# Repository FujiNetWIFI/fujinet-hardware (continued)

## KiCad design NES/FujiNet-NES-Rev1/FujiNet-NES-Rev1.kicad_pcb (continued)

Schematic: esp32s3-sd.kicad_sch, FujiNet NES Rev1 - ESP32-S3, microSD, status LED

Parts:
C42: 22uF; C_0805_2012Metric; MPN CL21A226MAQNNNE; LCSC C45783
C43, C46: 100nF; C_0603_1608Metric; MPN CC0603KRX7R9BB104; LCSC C14663
C44: 1uF; C_0603_1608Metric; MPN CL10A105KB8NNNC; LCSC C15849
C45: 10uF; C_0603_1608Metric; MPN CL10A106KP8NNNC; LCSC C19702
D3: WS2812B-2020-V6; LED_WS2812B-2020_PLCC4_2.0x2.0mm; MPN WS2812B-2020-V6; LCSC C52917434
J2: microSD; TF-SMD_TF-015; MPN TF-015; LCSC C113206
R17, R18: 10k; R_0603_1608Metric; MPN 0603WAF1002T5E; LCSC C25804
R19: 330R; R_0603_1608Metric; MPN 0603WAF3300T5E; LCSC C23138
RN1: 4x10k; R_Array_Convex_4x0603; MPN 4D03WGJ0103T5E; LCSC C29718
SW3: S3_RST; SW_SPST_TL3342; MPN TL3342F160QG; LCSC C2886898
SW4: S3_BOOT; SW_SPST_TL3342; MPN TL3342F160QG; LCSC C2886898
U4: ESP32-S3-WROOM-1-N16R8; ESP32-S3-WROOM-1; MPN ESP32-S3-WROOM-1-N16R8; LCSC C2913202

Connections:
+3V3: C42.1, C43.1, C45.1, J2.4 (VDD), R17.1, R18.1, RN1.5 (R4.2), RN1.6 (R3.2), RN1.7 (R2.2), RN1.8 (R1.2), U4.2 (3V3); also elsewhere on the board
+5V: C46.1, D3.4 (VDD); also elsewhere on the board
BOOTSEL_CTL: U4.5 (IO5); also elsewhere on the board
GND: C42.2, C43.2, C44.2, C45.2, C46.2, D3.2 (VSS), J2.6 (VSS), J2.10 (SH), J2.11 (SH), J2.12 (SH), J2.13 (SH), SW3.2, SW4.2, U4.1 (GND), U4.40 (GND), U4.41 (GND); also elsewhere on the board
LED_STRIP: R19.1, U4.25 (IO48)
RUN_CTL: U4.4 (IO4); also elsewhere on the board
S3_EN: C44.1, R17.2, SW3.1, U4.3 (EN); also elsewhere on the board
S3_IO0: SW4.1, U4.27 (IO0); also elsewhere on the board
S3_RXD: U4.36 (RXD0); also elsewhere on the board
S3_TXD: U4.37 (TXD0); also elsewhere on the board
SD_CD: J2.9 (CD), R18.2, U4.35 (IO42)
SD_CS: J2.2 (DAT3/CS), RN1.1 (R1.1), U4.34 (IO41)
SD_DAT1: J2.8 (DAT1), RN1.3 (R3.1)
SD_DAT2: J2.1 (DAT2), RN1.4 (R4.1)
SD_MISO: J2.7 (DAT0/DO), RN1.2 (R2.1), U4.33 (IO40)
SD_MOSI: J2.3 (CMD/DI), U4.31 (IO38)
SD_SCK: J2.5 (CLK), U4.32 (IO39)
USB_DM: U4.13 (USB_D-); also elsewhere on the board
USB_DP: U4.14 (USB_D+); also elsewhere on the board
WS_DIN: D3.3 (DIN), R19.2

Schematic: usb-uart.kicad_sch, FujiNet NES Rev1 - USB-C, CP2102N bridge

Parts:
C47: 1uF; C_0603_1608Metric; MPN CL10A105KB8NNNC; LCSC C15849
C48, C49: 100nF; C_0603_1608Metric; MPN CC0603KRX7R9BB104; LCSC C14663
C50: 4.7uF; C_0603_1608Metric; MPN CL10A475KO8NNNC; LCSC C19666
D4, D5, D6: ESD5Z5.0T1G; D_SOD-523; MPN ESD5Z5.0T1G; LCSC C82044
J3: USB-C; USB_C_Receptacle_HRO_TYPE-C-31-M-12; MPN TYPE-C-31-M-12; LCSC C165948
R20, R21: 5.1k; R_0603_1608Metric; MPN 0603WAF5101T5E; LCSC C23186
R22: 22k; R_0603_1608Metric; MPN 0603WAF2202T5E; LCSC C31850
R23: 47k; R_0603_1608Metric; MPN 0603WAF4702T5E; LCSC C25819
R24: 10k; R_0603_1608Metric; MPN 0603WAF1002T5E; LCSC C25804
U5: CP2102N-A02-GQFN28; QFN-28-1EP_5x5mm_P0.5mm_EP3.35x3.35mm; MPN CP2102N-A02-GQFN28R; LCSC C964632
U6: UMH3N; SOT-363_SC-70-6; MPN UMH3N; LCSC C62892

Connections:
+3V3: C49.1, C50.1, R24.1, U5.6 (VDD), U5.7 (VREGIN); also elsewhere on the board
CC1: J3.A5 (CC1), R20.1
CC2: J3.B5 (CC2), R21.1
CP_RST: R24.2, U5.9 (~RST)
GND: C47.2, C48.2, C49.2, C50.2, D4.2 (A), D5.2 (A), D6.2 (A), J3.A1 (GND), J3.A12 (GND), J3.B1 (GND), J3.B12 (GND), J3.SH (SHIELD), R20.2, R21.2, R23.2, U5.3 (GND), U5.23 (~CTS), U5.29 (GND); also elsewhere on the board
S3_EN: U6.6 (C1); also elsewhere on the board
S3_IO0: U6.3 (C2); also elsewhere on the board
S3_RXD: U5.26 (TXD); also elsewhere on the board
S3_TXD: U5.25 (RXD); also elsewhere on the board
UART_DTR: U5.28 (~DTR), U6.2 (B1), U6.4 (E2)
UART_RTS: U5.24 (~RTS), U6.1 (E1), U6.5 (B2)
UBRG_DM: D5.1 (K), J3.A7 (D-), J3.B7 (D-), U5.5 (D-)
UBRG_DP: D4.1 (K), J3.A6 (D+), J3.B6 (D+), U5.4 (D+)
VBUS: C47.1, C48.1, D6.1 (K), J3.A4 (VBUS), J3.A9 (VBUS), J3.B4 (VBUS), J3.B9 (VBUS), R22.1; also elsewhere on the board
VBUS_SNS: R22.2, R23.1, U5.8 (VBUS)

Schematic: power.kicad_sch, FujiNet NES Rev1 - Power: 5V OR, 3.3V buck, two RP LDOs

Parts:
C51, C55, C56: 100nF; C_0603_1608Metric; MPN CC0603KRX7R9BB104; LCSC C14663
C52, C53, C54, C57, C58: 22uF; C_0805_2012Metric; MPN CL21A226MAQNNNE; LCSC C45783
C59, C60, C61, C62: 1uF; C_0603_1608Metric; MPN CL10A105KB8NNNC; LCSC C15849
D7: SS34; D_SMA; MPN SS34; LCSC C8678
L3: 6.8uH; L_Sunlord_SWPA4030S; MPN SWPA4030S6R8MT; LCSC C62684
Q1: AO3401A; SOT-23; MPN AO3401A; LCSC C15127
R25: 4.7k; R_0603_1608Metric; MPN 0603WAF4701T5E; LCSC C23162
U7: AP63203WU; TSOT-23-6; MPN AP63203WU-7; LCSC C780769
U8, U9: AP2112K-3.3; SOT-23-5; MPN AP2112K-3.3TRG1; LCSC C51118

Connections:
+3V3: C57.1, C58.1, L3.2, U7.1 (FB); also elsewhere on the board
+3V3_RP: C60.1, U8.5 (VOUT); also elsewhere on the board
+3V3_RPB: C62.1, U9.5 (VOUT); also elsewhere on the board
+5V: C52.1, C53.1, C54.1, C55.1, C59.1, C61.1, D7.1 (K), Q1.2 (S), U7.2 (EN), U7.3 (IN), U8.1 (VIN), U8.3 (EN), U9.1 (VIN), U9.3 (EN); also elsewhere on the board
BUCK_BST: C56.2, U7.6 (BST)
BUCK_SW: C56.1, L3.1, U7.5 (SW)
CONS_5V: C51.1, Q1.3 (D); also elsewhere on the board
GND: C51.2, C52.2, C53.2, C54.2, C55.2, C57.2, C58.2, C59.2, C60.2, C61.2, C62.2, R25.2, U7.4 (GND), U8.2 (GND), U9.2 (GND); also elsewhere on the board
VBUS: D7.2 (A), Q1.1 (G), R25.1; also elsewhere on the board

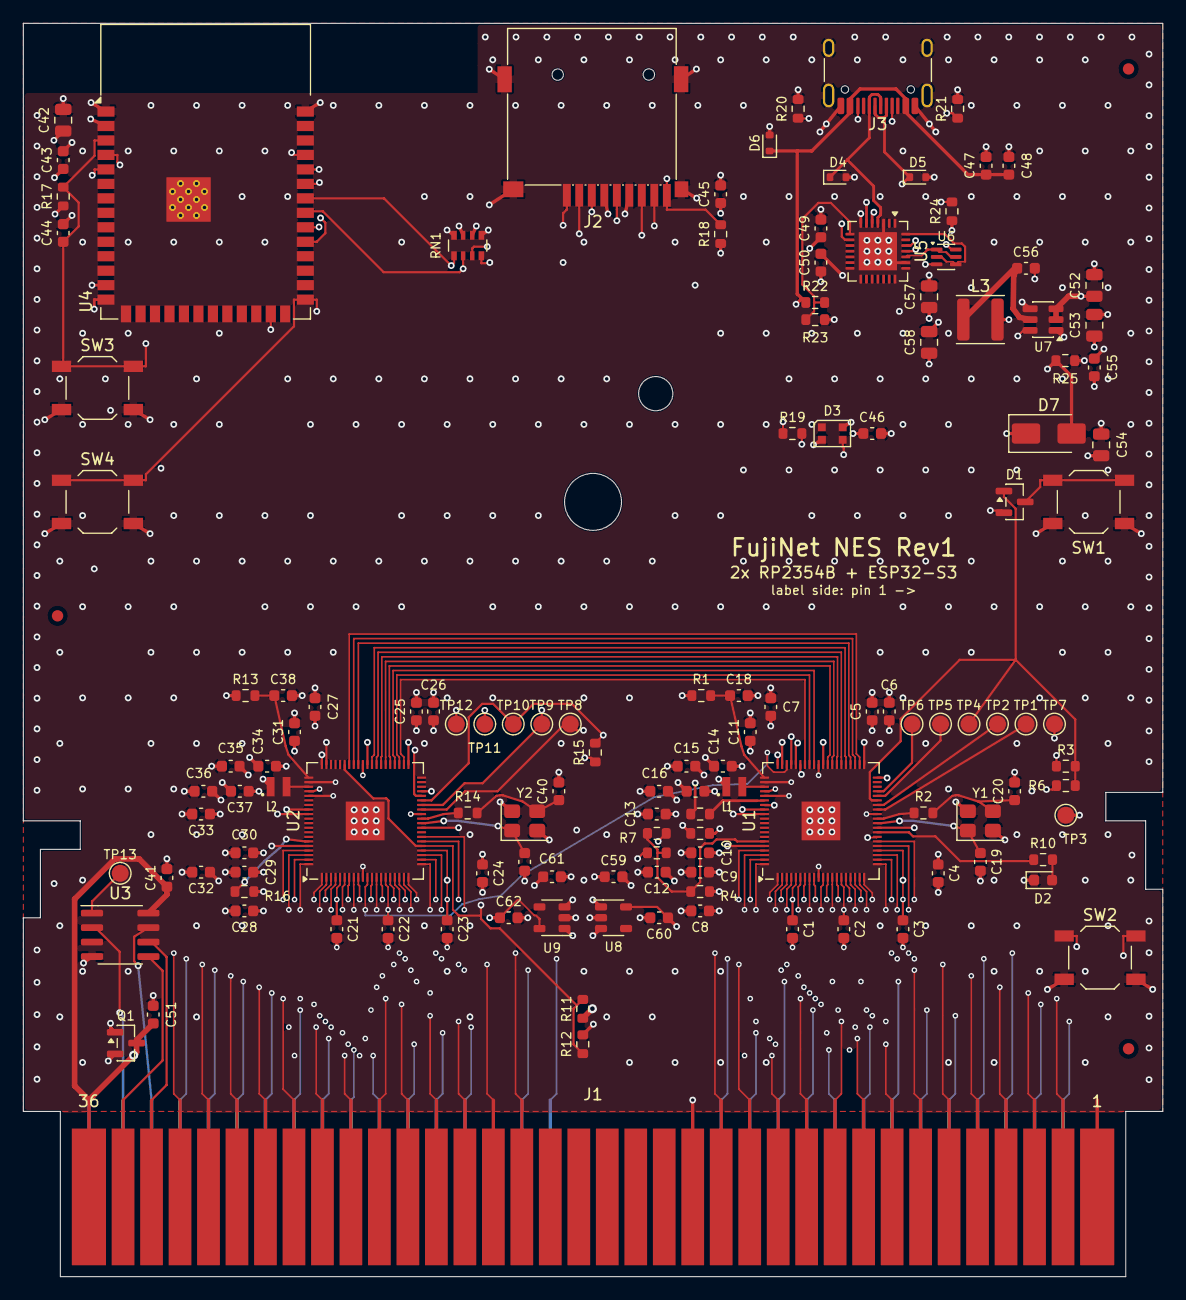
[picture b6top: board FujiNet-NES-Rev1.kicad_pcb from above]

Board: 6 copper layers, 100.0 x 110.0 mm, 133 parts (0 on the bottom side), 134 nets.

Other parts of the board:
FID1, FID2, FID3: Fiducial_1mm_Mask2mm

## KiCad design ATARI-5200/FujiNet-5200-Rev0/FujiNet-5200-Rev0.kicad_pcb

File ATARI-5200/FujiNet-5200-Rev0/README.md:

# FujiNet-5200 Rev0

An all-in-one **Atari 5200 FujiNet cartridge**: one board in the 36-pin cartridge slot that
carries both halves of the FujiNet stack.

**The cart half: RP2354B** (RP2350B + 2 MB flash, QFN-80) at 200 MHz.

- Runs the `fuji5200` cart firmware from `fujinet-firmware/pico/atari-5200`.
- Reads A0-A13 and the two cart enables (/EN40, /EN80) straight off the console's 5 V bus,
  through its 5 V-tolerant pads (GPIO0-15), and follows them as a mask ROM would.
- Puts each byte on GPIO16-23, into a **74HCT541** whose outputs are the edge's D0-D7.
- A **74HCT08 + 74HCT14** opens the '541 only while all three hold: an enable is low, the console
  is powered (PWR_OK), and the RP says it is serving (BUF_EN).
- A **74LVC1G17** squares the 2-port console's diode-isolated PHI2.

**The FujiNet half: ESP32-S3-WROOM-1-N16R8**, running the `fujiversal-atari5200` build of
fujinet-firmware.

- It is the RP's USB host on IO19/IO20, and it re-flashes the RP over PICOBOOT.
- USB-C: power, plus a CP2102N UART with UMH3N auto-program.
- microSD, a WS2812B status LED, and RESET / BOOTSEL / S3 EN / S3 BOOT buttons.

**Power:** +5V is the OR of three sources:

- the console's 5 V, through a P-FET;
- USB VBUS;
- the universal consoles' raw adapter DC on edge pin 11, through a 5 V buck.

The console path switches off whenever either of the other two is present.

**Status (2026-10-09):** schematic regenerated and audited; board placed, routed and packaged for
JLCPCB and PCBWay. Not yet built. See *Before ordering* and *Bring-up*.

| Check | Result |
|---|---|
| ERC, all severities | 0 |
| `tools/check_nets.py`: netlist vs `a52_cart.h`, the CX5200 FSM edge map, the S3 pin map, FT-pad rules | 366 / 366 |
| `tools/check_glue.py`: the '541 enables vs `a52_glue_drive()`, every input | 16 / 16 |
| Netlist parity: drawn sheets vs `design.py`, names included | every net |
| Mirror check: each sheet's parts in board order | tau 1.00 on all five sheets |
| `tools/audit/edge_orientation.py` | OK |
| Deep review (kicad-happy evidence gate) | 30 / 30 findings verified against datasheet pages |
| kicad-happy SPICE + `tools/audit/spice_checks.py` | 21 / 21; PHI2, PWR_OK and console-gate decks pass |
| DRC with schematic parity, all severities | 0 violations, 0 unconnected, 0 parity issues |
| `tools/audit/check_fab.py` / `check_gerbers.py` | 14 / 14 / all pass |
| JLCPCB stock (`tools/audit/sourcing.py`) | 46 lines, 0 short for 5 boards; ~US$17 of parts per board |

## Sheets

The schematic is drawn the way the board is built. Every sheet is the board turned so that the
fingers face left (board south -> page left, north -> right, west -> top, east -> bottom), with
each part where it sits on the board. Signals flow left to right, from the cartridge slot to the
USB-C. `tools/sch_place.py` holds every sheet to the board's order.

| Page | Sheet | Contents |
|---|---|---|
| 1 | root | the board outline with a block per sheet, the nine signals between sheets, notes |
| 2 | `cart-bus` | the 36-pin edge, 74HCT541, the '08 / '14 glue, the RP2354B's GPIOs, PHI2 buffer, interlock, PWR_OK and ADC senses, debug UART, scope pads |
| 3 | `rp-core` | RP2354B supplies and decoupling ring, core regulator, crystal, SWD, RUN / BOOTSEL, USB to the S3 |
| 4 | `fujinet` | ESP32-S3, microSD, WS2812B, S3 EN / BOOT |
| 5 | `usb` | USB-C, CP2102N, auto-program pair |
| 6 | `power` | the three-source +5V OR, the raw-DC buck, the 3.3 V buck, the RP's LDO |

## Edge connector

The edge pinout is taken from Atari's CX5200 Field Service Manual (Rev 4, 1983). It has
schematics of CA018087 (the original 4-port), CA020108 (the universal 4-port) and CA021374 (the
2-port).

The geometry is from Grand Idea Studio's Pixels Past gerbers, tdididit's a52 library, sanni's
cartreader adapter, and the Sullins connector datasheet. `tools/audit/edge_orientation.py`
checks the footprint against them.

| Pin | Signal | Net | Pin | Signal | Net |
|---|---|---|---|---|---|
| 1-8 | D0-D7 | '541 Y | 19, 20 | A0, A1 | GPIO0, 1 |
| 9 | /Enable $80-$BF | EN80_N | 21, 22 | A3, A4 | GPIO3, 4 |
| 10 | /Enable $40-$7F | EN40_N | 23 | GND (shield) | GND |
| 11 | raw DC (universal boards) | UNREG -> JP2 -> PTC -> buck | 24 | GND (CA018087) / video in (universal) | **open** |
| 12, 13 | GND | GND | 25 | GND | GND |
| 14 | GND (CA018087) / PHI2 (2-port, via CR9) | PHI2 -> 74LVC1G17 | 26 | +5 V from VR1 | CONS_5V |
| 15, 16, 17 | A6, A5, A2 | GPIO6, 5, 2 | 27, 29, 31 | A7, A8, A9 | GPIO7, 8, 9 |
| 18 | CI1, interlock (short finger) | ILK_A, JP1 | 28, 30 | NC, OSC (universal) | **open** |
| | | | 32-35 | A13, A10, A12, A11 | GPIO13, 10, 12, 11 |
| | | | 36 | CI2, interlock (short finger) | ILK_B, JP1 |

**Faces.** Pins 1-18 are on the label face, which is F.Cu, the component side. Pin 1 (D0) is at
the left when seen from that face with the fingers down. Pin 37-k sits behind pin k.

**Short fingers.** Pins 18 and 36 start 1.9 mm from the edge; the others start at 0.6 mm. They
make contact last and break first, as on every stock cart.

**No R/W, and the enables are not PHI2-qualified.** The enables are plain 74LS139 decodes of A14
/ A15. The cart answers reads only, and the '541 drives whenever an enable is low, exactly as a
stock ROM does.

**Never ground 11, 24, 28 or 30.**

- 11 is the adapter's raw DC on the universal boards, live even with the console switched off.
- 24 is the VCS adaptor's video input on the universal boards.
- 30 goes into the colour oscillator.

## RP2354B pin map

The pin map is exactly `a52_cart.h`. `tools/check_nets.py` reads every `*_PIN` define and fails
if the header names a pin this board does not wire, or the board wires one the header does not
name.

| GPIO | Net | Goes to |
|---|---|---|
| 0-13 | A0-A13 | the edge, directly |
| 14, 15 | EN40_N, EN80_N | edge 10, 9; also the 74HCT08 |
| 16-23 | RP_D0-7 | 74HCT541 A8..A1 (channels reversed; outputs only) |
| 24 | PWR_OK | 74HCT14 output (console 5 V sense) |
| 25 | PHI2_RP | 74LVC1G17 output (2-port only) |
| 26 | BUF_EN | the glue; R25 4.7k pull-down (RP2350-E9) |
| 27 | RP_LED | 1k, red LED |
| 28 | ILK | the DNP interlock switch's driver |
| 40 | VSENSE_ADC | ADC0: CONS_5V through 100k / 100k (0.5 x), 100 nF |
| 44, 45 | DBG_TX, DBG_RX | J4 (DNP), 3.3 V only |

- GPIO40-47 are not 5 V tolerant. `check_nets.py` asserts that only passives and the 3.3 V debug
  header reach them.
- The bus inputs have no pulls. The firmware turns the pad pulls off (RP2350 erratum E9).

## Glue

`a52_glue_drive()`: `drive = !(en40_n && en80_n) && pwrok && bufen`.

```
/OE1 = EN_ANY_N = /EN40 AND /EN80        74HCT08: either enable low
/OE2 = SERVE_N  = NOT(PWR_OK AND BUF_EN) 74HCT08 + 74HCT14: console powered and the RP serving
```

- **PWR_OK.** CONS_5V goes through 22k / 100k into a 74HCT14 Schmitt and is inverted twice. It
  is high once the console rail passes 2.3-2.6 V.
- **BUF_EN.** A 4.7k pull-down keeps the '541 shut until the firmware drives GPIO26. That is
  under the 8.2k the RP2350-E9 latch needs.
- **PHI2 (2-port).** The console reaches pin 14 through CR9, a 1N914 with its anode at the pin,
  so it can only pull PHI2 low, to 0.94-1.09 V. R29 4.7k pulls the pin up to CONS_5V, and U11, a
  74LVC1G17 at 5 V, squares it: VT- min 1.32 V, +0.24 V of margin at the worst corner.

  The pull-up goes to CONS_5V and not +5V. With the console off and USB on, a pull-up to +5V
  would feed the console's LS125 through CR9.

## Power

**Q3, AO3401A: console 5 V -> +5V.** D = CONS_5V, S = +5V, gate = CONS_OFF.

- CONS_OFF = VBUS OR PRE5V, through D9 (BAT54C), with R23 100k to GND.
- The console path is fully on whenever the console alone powers the cart.
- R3 and R22, 4.7k each, keep the SS34s' reverse leakage off the OR. At 500 uA each, VGS is still
  -2.9 V.

**D4, SS34: USB VBUS -> +5V.**

**Edge 11 raw DC -> +5V.** The chain is:

1. JP2, a bridged jumper. Cut it to take nothing from pin 11.
2. F1, a 0.35 A / 30 V PTC.
3. R30, 2.2R, to limit inrush when the cart goes in with the adapter live.
4. U10, an AP63205 (5 V, 3.8-32 V in).
5. D8, an SS34.

On the universal consoles this takes the whole cart off VR1.

**+5V feeds:**

- the '541, '08, '14 and LVC1G17;
- the WS2812B;
- the AP2112K LDO (+3V3_RP, every RP2354B supply pin), which rises with +5V;
- the AP63203 buck (+3V3: S3, microSD, CP2102N).

**Budget:** ~470 mA at a WiFi TX burst, ~170 mA on average (`tools/audit/margins.py`).

**Warning: the original 4-port console (CA018087).** VR1 there is a **0.5 A 78M05** that also
feeds the console's RAM and controllers, and that board has no raw DC on pin 11. Without USB, a
WiFi burst can pull VR1 into current limit. On those consoles, run with USB-C plugged in for
WiFi. The universal consoles (CA020108, CA021374) feed the cart from the adapter instead.

## Interlock

Pins 18 and 36 are shorted by **JP1**, a bridged solder jumper, as a stock cartridge shorts them.
The stock jumper closes Q8 / Q6's base circuit (34-61 mA at ~0.2 V), which switches VR1 on.

Beside JP1, all DNP:

- **Q2**, a 2N7002 low-side switch: D on 36, S on 18, gate pulled to +5V by R26.
- **Q1**, a 2N7002 driver on GPIO28.
- **R24**, a 4.7k pull-down on GPIO28.

To let the firmware open the interlock (a console power cycle), cut JP1 and fit them. The cart
must then be powered from USB or the raw DC first, since VR1 is what that switch turns on.

## Board

**Outline.** T-shaped, 84 x 98 mm (`tools/placement.py`, `docs/floorplan-study.md`):

- the 47.8 mm tab;
- the original cart board's 61 mm lower body, up to 38 mm from the edge;
- a 45-degree step out to the 84 mm upper body that carries the FujiNet half.

It needs a custom shell. The stock 5200 shell holds a 61 x 89.5 mm board between ribs.
`case/board-anchors.scad` gives a shell design the outline, the three screws, the button
pinholes, the LEDs, the USB-C / microSD / antenna openings and a label recess.

**Stack-up.** 6 layers, 1.6 mm:

| Layer | Use |
|---|---|
| F.Cu | every part; fingers 1-18; signals and a GND pour |
| In1 | GND |
| In2, In3 | signals |
| In4 | power: +3V3 north; a +5V island south and east; +3V3_RP under the RP2354B ring; DVDD under its core |
| B.Cu | fingers 19-36; signals and a GND pour |

**Data path.** The 74HCT541 stands over the D0-D7 fingers, and its channels are taken in
reverse, so finger -> '541 -> RP GPIO16-23 crosses nothing on F.Cu.

## Fab packages

`tools/export.py` writes them, and `tools/audit/check_fab.py` / `check_gerbers.py` check them.

- `exports/jlcpcb/`: `ORDER-JLCPCB.md`, gerbers with an order-number spot, `BOM-JLCPCB.csv`, and
  `CPL-JLCPCB.csv` with rotations corrected to each LCSC part's EasyEDA footprint
  (`tools/audit/jlc/`, measured pad by pad).
- `exports/pcbway/`: `ORDER-PCBWay.md`, gerbers, `BOM-PCBWay.csv` (MPN / manufacturer),
  `Centroid-PCBWay.csv` (KiCad's own rotations), and `Assembly-top.pdf`.

Both need:

- 6 layers, 1.6 mm, ENIG;
- **hard gold fingers with a 30-45 degree bevel** on the 47.8 mm tab edge only;
- via-in-pad filled and capped under the RP2354B;
- top-side assembly.

## Before ordering

1. **The tab.** Print `docs/tab-overlay-1to1.pdf` at 100 % and check its 50 mm ruler. Lay a real
   5200 cartridge board on it:
   - pins 1-18 on the label side, pin 1 at the left;
   - the finger span, the 47.8 mm tab and the two short fingers must match.
2. **Thickness.** The console connector takes 1.57 +/- 0.2 mm. 1.6 mm is ordered.
3. **Stock.** Re-run `tools/audit/sourcing.py` on the order day.
4. **The preview.** In JLCPCB's placement preview, check:
   - pin 1 of the RP2354B, the '541 (TSSOP-20), the '08 / '14, the LVC1G17 (SOT-353), the
     regulators, the CP2102N, USB-C and the microSD;
   - the polarity of the diodes and the WS2812B.

## Bring-up

1. **Power, no console.**
   - USB-C only: +5V is 4.3-4.9 V at TP2, +3V3 at TP1, +3V3_RP at TP11, DVDD 1.1 V at TP3.
   - CONS_5V (TP17) and PRE5V (TP16) stay at 0 V.
2. **In a 2-port or universal 4-port, USB unplugged.**
   - With the adapter in, TP18 (raw DC after the PTC) reads 9-13 V and PRE5V 5.0 V.
   - The console path is off: CONS_5V carries only the console's own 5 V.
   - Cut JP2 and the cart runs from CONS_5V instead.
3. **In an original 4-port (CA018087), USB unplugged.** Measure CONS_5V at TP17 during WiFi TX.
   If VR1 sags, run WiFi on USB power, or cap the S3's TX power in firmware.
4. **Bus.** Scope /EN40, /EN80 (TP8 / TP9), /OE1 / /OE2 (TP10 / TP13), PWR_OK (TP14) and D0.
   Check:
   - the '541 opens only inside an enable;
   - D0 settles well before the end of the cycle (`timing_margins.py`: +234 ns budget).
5. **PHI2 (2-port).** At TP15 the pin sits at ~1 V low and ~4.8 V high. PHI2_RP (GPIO25) is a
   clean 0 / 5 V square.
6. **Power-on race.** Measure the RP's cold boot to a serving core1 against the 5200 BIOS's first
   cart read (scope BUF_EN against /EN80 at power-on). USB-C power before the console avoids the
   race.

## Flashing

- **The S3:** over USB-C (CP2102N, esptool auto-program).
- **The RP:**
  - by the S3 over PICOBOOT: IO4 -> 1k -> RUN, IO5 -> 1k -> QSPI_SS, low to assert;
  - by hand: hold BOOTSEL (SW2) and press RESET (SW1);
  - over SWD: TP4 SWCLK, TP5 SWDIO, TP6 GND, TP7 RUN.
- **The RP's debug UART:** J4 (DNP, 3-pin 2.54 mm, 3.3 V).

## Firmware follow-ups (not changed here)

- **fn-5200-board `fujiversal-atari5200.h`:**
  - add `PIN_RP2040_RUN` = IO4 and `PIN_RP2040_BOOTSEL` = IO5, which this board wires;
  - set `PIN_CARD_DETECT` to IO42 (the microSD card-detect, 10k pull-up).
- **`a52_cart.h`:** `VSENSE_PIN`'s comment says "12 V-safe divider". Pin 26 is 5 V and the
  divider is 0.5 x. Nothing reads the ADC yet. It could watch VR1 sag during WiFi.
- **`main.c`:** nothing initialises GPIO44/45 (J4).
- **S3:** cap the TX power when the cart runs from VR1 alone (an original 4-port without USB).

## Regenerating

You need KiCad 10.0.6, Python 3 with numpy, a C compiler (for `check_glue.py`), ngspice and
poppler for the audits, and Java with Freerouting 2.4.1 for the board.

```sh
tools/build_all.sh                 # footprints, sheets, ERC, check_nets / check_glue / edge, BOM, PDF, fab packages
LAYOUT=1 tools/build_all.sh        # ... and place, route (tools/route_board.sh) and DRC the board
tools/audit/run_sch_audit.sh       # kicad-happy schematic audit, SPICE, margins, timing, deep review
tools/audit/run_pcb_audit.sh       # kicad-happy PCB, cross, EMC, thermal, gerbers, release gate
```

`check_*.py` read two external sources:

- `$FUJINET_FIRMWARE/pico/atari-5200` (default `~/Workspace/fujinet-firmware`, branch
  `add-5200`);
- the S3 pin map from `$FUJINET_A52_BOARD/include/pinmap/fujiversal-atari5200.h` (default
  `~/Workspace/fn-5200-board`).

Never edit the KiCad files; edit these instead:

| File | What it holds |
|---|---|
| `tools/design.py` | the circuit |
| `tools/sch_layout.py` | the drawing |
| `tools/placement.py` | the floorplan |
| `tools/edge_geom.py` | the edge |

References are geographic and frozen in `tools/refs.lock`. Net names are frozen in
`tools/nets.lock`.

## Provenance and license

**CERN-OHL-W-2.0.**

- **This repository:** the RP2354B core, the FujiNet sheets, the power OR and the generators come
  from FujiNet-SMS Rev0 / FujiNet-7800 Rev0 in this repository, which descend from NES Rev0,
  Astrocade Rev0, INTV Rev0 and the PiNTY CARD.
- **Raspberry Pi:** the AOTA inductor footprint is from Raspberry Pi's RP2350 minimal design (MIT,
  `tools/RPI-MINIMAL-LICENSE.txt`).
- **Edge facts:** Atari CX5200 Field Service Manual; Pixels Past rev B gerbers; tdididit a52
  library; sanni cartreader.
- **Glue and pin map:** `fujinet-firmware` `pico/atari-5200` `a52_cart.h`.
- **Symbols:** official KiCad libraries (CC-BY-SA 4.0 with exception), except the project's own
  (the 5200 edge, the RP2354B and ESP32-S3 functional units, the USB-C 16P, the TF-015 microSD).

## Files

| Path | Contents |
|---|---|
| `FujiNet-5200-Rev0.kicad_pro/.kicad_sch/.kicad_pcb` | KiCad 10 project: root + `cart-bus`, `rp-core`, `fujinet`, `usb`, `power`; the routed board |
| `FujiNet-5200.kicad_sym`, `FujiNet-5200.pretty/`, `3d/` | project symbols, footprints, 3D models |
| `FujiNet-5200-Rev0-BOM.csv` | grouped BOM (MPN, manufacturer, LCSC; DNP flagged) |
| `exports/jlcpcb/`, `exports/pcbway/` | the fab packages |
| `docs/` | schematic PDF, layout SVGs, renders, tab overlay, design review, floorplan study, sourcing |
| `case/board-anchors.scad` | the board's outline and openings, for a shell |
| `tools/` | generators, routing pipeline, checks, audits |

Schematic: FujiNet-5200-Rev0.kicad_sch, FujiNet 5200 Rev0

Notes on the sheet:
edge fingers: the console slot
FujiNet for the Atari 5200 SuperSystem, Rev0: RP2354B on the cart bus + ESP32-S3. This page is the board seen from its component side (the label face), turned so that the edge fingers face left (board south -> page left, north -> right, west -> top, east -> bottom), 2:1, each sheet's block where it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

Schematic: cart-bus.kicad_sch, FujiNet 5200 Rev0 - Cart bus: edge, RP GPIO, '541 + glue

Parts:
C9, C40, C41, C49, C52: 100nF; C_0603_1608Metric; MPN CC0603KRX7R9BB104; LCSC C14663
C42: 10uF; C_0603_1608Metric; MPN CL10A106KP8NNNC; LCSC C19702
D7: red; LED_0603_1608Metric; MPN KT-0603R; LCSC C2286
J1: Atari5200_Cart_Edge_36
J4: DBG UART; PinHeader_1x03_P2.54mm_Vertical; MPN PZ254V-11-03P; LCSC C2937625; not fitted
JP1: ILK; SolderJumper-2_P1.3mm_Bridged_RoundedPad1.0x1.5mm
Q1, Q2: 2N7002; SOT-23; MPN 2N7002; LCSC C8545; not fitted
R7, R8, R28: 100k; R_0603_1608Metric; MPN 0603WAF1003T5E; LCSC C25803
R20: 1k; R_0603_1608Metric; MPN 0603WAF1001T5E; LCSC C21190
R24: 4.7k; R_0603_1608Metric; MPN 0603WAF4701T5E; LCSC C23162; not fitted
R25, R29: 4.7k; R_0603_1608Metric; MPN 0603WAF4701T5E; LCSC C23162
R26: 10k; R_0603_1608Metric; MPN 0603WAF1002T5E; LCSC C25804; not fitted
R27: 22k; R_0603_1608Metric; MPN 0603WAF2202T5E; LCSC C31850
TP8: /EN40; TestPoint_Pad_D1.5mm
TP9: /EN80; TestPoint_Pad_D1.5mm
TP10: /OE1; TestPoint_Pad_D1.5mm
TP12: GND; TestPoint_Pad_D1.5mm
TP13: /OE2; TestPoint_Pad_D1.5mm
TP14: PWR_OK; TestPoint_Pad_D1.5mm
TP15: PHI2; TestPoint_Pad_D1.5mm
U5: RP2354B; QFN-80-1EP_10x10mm_P0.4mm_EP3.4x3.4mm; MPN RP2354B; LCSC C39843328
U7: 74HCT541; TSSOP-20_4.4x6.5mm_P0.65mm; MPN SN74HCT541PWR; LCSC C436096
U8: 74HCT08; SOIC-14_3.9x8.7mm_P1.27mm; MPN SN74HCT08DR; LCSC C6767
U9: 74HCT14; SOIC-14_3.9x8.7mm_P1.27mm; MPN SN74HCT14DR; LCSC C6769
U11: 74LVC1G17; SOT-353_SC-70-5; MPN 74LVC1G17GW,125; LCSC C426705

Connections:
+5V: C40.1, C41.1, C42.1, C49.1, C52.1, R26.1, U7.20 (VCC), U8.14 (VCC), U9.14 (VCC), U11.5 (VCC); also elsewhere on the board
/UNREG: J1.11 (UNREG); also elsewhere on the board
/cart-bus/A0: J1.19 (A0), U5.77 (GPIO0)
/cart-bus/A1: J1.20 (A1), U5.78 (GPIO1)
/cart-bus/A2: J1.17 (A2), U5.79 (GPIO2)
/cart-bus/A3: J1.21 (A3), U5.80 (GPIO3)
/cart-bus/A4: J1.22 (A4), U5.1 (GPIO4)
/cart-bus/A5: J1.16 (A5), U5.2 (GPIO5)
/cart-bus/A6: J1.15 (A6), U5.3 (GPIO6)
/cart-bus/A7: J1.27 (A7), U5.4 (GPIO7)
/cart-bus/A8: J1.29 (A8), U5.6 (GPIO8)
/cart-bus/A9: J1.31 (A9), U5.7 (GPIO9)
/cart-bus/A10: J1.33 (A10), U5.8 (GPIO10)
/cart-bus/A11: J1.35 (A11), U5.9 (GPIO11)
/cart-bus/A12: J1.34 (A12), U5.11 (GPIO12)
/cart-bus/A13: J1.32 (A13), U5.12 (GPIO13)
/cart-bus/BUF_EN: R25.1, U5.27 (GPIO26), U8.4
/cart-bus/D0: J1.1 (D0), U7.11 (Y7)
/cart-bus/D1: J1.2 (D1), U7.12 (Y6)
/cart-bus/D2: J1.3 (D2), U7.13 (Y5)
/cart-bus/D3: J1.4 (D3), U7.14 (Y4)
/cart-bus/D4: J1.5 (D4), U7.15 (Y3)
/cart-bus/D5: J1.6 (D5), U7.16 (Y2)
/cart-bus/D6: J1.7 (D6), U7.17 (Y1)
/cart-bus/D7: J1.8 (D7), U7.18 (Y0)
/cart-bus/DBG_RX: J4.2, U5.56 (GPIO45/ADC5)
/cart-bus/DBG_TX: J4.1, U5.55 (GPIO44/ADC4)
/cart-bus/EN40_N: J1.10 (~EN40), TP8.1, U5.13 (GPIO14), U8.1
/cart-bus/EN80_N: J1.9 (~EN80), TP9.1, U5.14 (GPIO15), U8.2
/cart-bus/EN_ANY_N: TP13.1, U7.19 (G2), U8.3
/cart-bus/ILK: Q1.1 (G), R24.1, U5.36 (GPIO28)
/cart-bus/ILK_A: J1.18 (CI1), JP1.1 (A), Q2.2 (S)
/cart-bus/ILK_B: J1.36 (CI2), JP1.2 (B), Q2.3 (D)
/cart-bus/ILK_G: Q1.3 (D), Q2.1 (G), R26.2
/cart-bus/PHI2: J1.14 (PHI2/GND), R29.2, TP15.1, U11.2
/cart-bus/PHI2_RP: U5.26 (GPIO25), U11.4
/cart-bus/PWR_OK: TP14.1, U5.25 (GPIO24), U8.5, U9.4
/cart-bus/PWR_OK_N: U9.2, U9.3
/cart-bus/RP_D0: U5.16 (GPIO16), U7.9 (A7)
/cart-bus/RP_D1: U5.17 (GPIO17), U7.8 (A6)
/cart-bus/RP_D2: U5.18 (GPIO18), U7.7 (A5)
/cart-bus/RP_D3: U5.19 (GPIO19), U7.6 (A4)
/cart-bus/RP_D4: U5.20 (GPIO20), U7.5 (A3)
/cart-bus/RP_D5: U5.21 (GPIO21), U7.4 (A2)
/cart-bus/RP_D6: U5.22 (GPIO22), U7.3 (A1)
/cart-bus/RP_D7: U5.23 (GPIO23), U7.2 (A0)
/cart-bus/RP_LED: R20.1, U5.28 (GPIO27)
/cart-bus/RP_LED_A: D7.2 (A), R20.2
/cart-bus/SERVE: U8.6, U9.5
/cart-bus/SERVE_N: TP10.1, U7.1 (G1), U9.6
/cart-bus/VSENSE: R27.2, R28.1, U9.1
/cart-bus/VSENSE_ADC: C9.1, R7.2, R8.1, U5.49 (GPIO40/ADC0)
CONS_5V: J1.26 (+5V), R7.1, R27.1, R29.1; also elsewhere on the board
GND: C9.2, C40.2, C41.2, C42.2, C49.2, C52.2, D7.1 (K), J1.12 (GND), J1.13 (GND), J1.23 (GND), J1.25 (GND), J4.3, Q1.2 (S), R8.2, R24.2, R25.2, R28.2, TP12.1, U7.10 (GND), U8.7 (GND), U8.9, U8.10, U8.12, U8.13, U9.7 (GND), U9.9, U9.11, U9.13, U11.3 (GND); also elsewhere on the board

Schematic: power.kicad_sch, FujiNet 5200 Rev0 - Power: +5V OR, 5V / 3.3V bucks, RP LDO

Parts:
C10, C13, C43, C46, C50: 100nF; C_0603_1608Metric; MPN CC0603KRX7R9BB104; LCSC C14663
C11, C12, C21, C22, C23, C44, C45, C47, C48: 22uF; C_0805_2012Metric; MPN CL21A226MAQNNNE; LCSC C45783
C33, C35: 1uF; C_0603_1608Metric; MPN CL10A105KB8NNNC; LCSC C15849
C51: 10uF; C_0603_1608Metric; MPN CL10A106KP8NNNC; LCSC C19702
D4, D8: SS34; D_SMA; MPN SS34; LCSC C8678
D9: BAT54C; SOT-23; MPN BAT54C,215; LCSC C37704
F1: 0.35A; Fuse_1206_3216Metric; MPN 1206L035/30WR; LCSC C2153989
JP2: RAWDC; SolderJumper-2_P1.3mm_Bridged_RoundedPad1.0x1.5mm
L1: 6.8uH; L_Sunlord_SWPA4030S; MPN SWPA4030S6R8MT; LCSC C62684
L3: 4.7uH; L_Sunlord_SWPA4030S; MPN SWPA4030S4R7MT; LCSC C57269
Q3: AO3401A; SOT-23; MPN AO3401A; LCSC C15127
R3, R22: 4.7k; R_0603_1608Metric; MPN 0603WAF4701T5E; LCSC C23162
R23: 100k; R_0603_1608Metric; MPN 0603WAF1003T5E; LCSC C25803
R30: 2.2R; R_0603_1608Metric; MPN RC0603FR-072R2L; LCSC C112307
TP1: +3V3; TestPoint_Pad_D1.5mm
TP2: +5V; TestPoint_Pad_D1.5mm
TP11: +3V3_RP; TestPoint_Pad_D1.5mm
TP16: PRE5V; TestPoint_Pad_D1.5mm
TP17: CONS_5V; TestPoint_Pad_D1.5mm
TP18: RAWDC; TestPoint_Pad_D1.5mm
U4: AP63203WU; TSOT-23-6; MPN AP63203WU-7; LCSC C780769
U6: AP2112K-3.3; SOT-23-5; MPN AP2112K-3.3TRG1; LCSC C51118
U10: AP63205WU; TSOT-23-6; MPN AP63205WU-7; LCSC C2071056

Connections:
+3V3: C21.1, C22.1, L1.2, TP1.1, U4.1 (FB); also elsewhere on the board
+3V3_RP: C35.1, TP11.1, U6.5 (VOUT); also elsewhere on the board
+5V: C11.1, C12.1, C13.1, C23.1, C33.1, D4.1 (K), D8.1 (K), Q3.2 (S), TP2.1, U4.2 (EN), U4.3 (IN), U6.1 (VIN), U6.3 (EN); also elsewhere on the board
/UNREG: JP2.1 (A); also elsewhere on the board
/power/BUCK_BST: C10.2, U4.6 (BST)
/power/BUCK_SW: C10.1, L1.1, U4.5 (SW)
/power/CONS_OFF: D9.3, Q3.1 (G), R23.1
/power/PRE5V: C47.1, C48.1, D8.2 (A), D9.2, L3.2, R22.1, TP16.1, U10.1 (FB)
/power/PRE_BST: C43.2, U10.6 (BST)
/power/PRE_SW: C43.1, L3.1, U10.5 (SW)
/power/PRE_VIN: C44.1, C45.1, C46.1, R30.2, U10.2 (EN), U10.3 (IN)
/power/UNREG_F: F1.2, R30.1, TP18.1
/power/UNREG_J: F1.1, JP2.2 (B)
CONS_5V: C50.1, C51.1, Q3.3 (D), TP17.1; also elsewhere on the board
GND: C11.2, C12.2, C13.2, C21.2, C22.2, C23.2, C33.2, C35.2, C44.2, C45.2, C46.2, C47.2, C48.2, C50.2, C51.2, R3.2, R22.2, R23.2, U4.4 (GND), U6.2 (GND), U10.4 (GND); also elsewhere on the board
VBUS: D4.2 (A), D9.1, R3.1; also elsewhere on the board

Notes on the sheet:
PWR_FLAG: these rails reach their loads only through passive parts (the edge fingers, USB-C, the P-FET, the SS34s, the bucks' inductors).
Power tree: +5V is the OR of three sources. CONS_5V edge 26, the console's VR1 (a 78M05, 0.5 A, on the original CA018087 board, which also feeds the console's RAM and controllers), through Q3 AO3401A (D = CONS_5V, S = +5V): on unless its gate CONS_OFF is high; with the gate high only its body diode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

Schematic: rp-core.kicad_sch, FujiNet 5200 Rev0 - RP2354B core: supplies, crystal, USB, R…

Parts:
C14, C15, C17, C18, C19, C20, C26, C28, C29, C34, C36, C37, C38, C39: 100nF; C_0603_1608Metric; MPN CC0603KRX7R9BB104; LCSC C14663
C16, C25, C27: 4.7uF; C_0603_1608Metric; MPN CL10A475KO8NNNC; LCSC C19666
C24: 10uF; C_0603_1608Metric; MPN CL10A106KP8NNNC; LCSC C19702
C30, C31: 15pF; C_0603_1608Metric; MPN CL10C150JB8NNNC; LCSC C1644
D5: BAT54C; SOT-23; MPN BAT54C,215; LCSC C37704
L2: 3.3uH; RPI_L_AOTA-B201610S3R3; MPN AOTA-B201610S3R3-101-T; LCSC C42411119
R9, R14, R15, R18: 1k; R_0603_1608Metric; MPN 0603WAF1001T5E; LCSC C21190
R12: 33R; R_0603_1608Metric; MPN 0603WAF330JT5E; LCSC C23140
R13, R21: 10k; R_0603_1608Metric; MPN 0603WAF1002T5E; LCSC C25804
R16, R17: 27R; R_0603_1608Metric; MPN 0603WAF270JT5E; LCSC C25190
SW1: RESET; SW_SPST_TS-1187A; MPN TS-1187A-B-A-B; LCSC C318884
SW2: BOOTSEL; SW_SPST_TS-1187A; MPN TS-1187A-B-A-B; LCSC C318884
TP3: DVDD; TestPoint_Pad_D1.5mm
TP4: SWCLK; TestPoint_Pad_D1.5mm
TP5: SWDIO; TestPoint_Pad_D1.5mm
TP6: GND; TestPoint_Pad_D1.5mm
TP7: RUN; TestPoint_Pad_D1.5mm
U5: RP2354B; QFN-80-1EP_10x10mm_P0.4mm_EP3.4x3.4mm; MPN RP2354B; LCSC C39843328
Y1: 12MHz; Crystal_SMD_3225-4Pin_3.2x2.5mm; MPN ABM8-272-T3; LCSC C20625731

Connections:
+3V3_RP: C17.1, C18.1, C19.1, C20.1, C24.1, C25.1, C28.1, C29.1, C34.1, C36.1, C37.1, C38.1, C39.1, R12.1, R13.1, R21.1, U5.5 (IOVDD), U5.15 (IOVDD), U5.24 (IOVDD), U5.29 (IOVDD), U5.41 (IOVDD), U5.50 (IOVDD), U5.59 (ADC_AVDD), U5.60 (IOVDD), U5.64 (VREG_VIN), U5.68 (USB_OTP_VDD), U5.69 (QSPI_IOVDD), U5.76 (IOVDD); also elsewhere on the board
/BOOTSEL_CTL: R15.1; also elsewhere on the board
/RUN_CTL: R9.1; also elsewhere on the board
/S3_EN: D5.2; also elsewhere on the board
/USB_DM: R17.1; also elsewhere on the board
/USB_DP: R16.1; also elsewhere on the board
/rp-core/BOOTSEL_BTN: R14.2, SW2.1
/rp-core/QSPI_SS: R14.1, R15.2, R21.2, U5.75 (~QSPI_SS)
/rp-core/RP_LX: L2.2, U5.63 (VREG_LX)
/rp-core/RP_USB_DM: R17.2, U5.66 (USB_DM)
/rp-core/RP_USB_DP: R16.2, U5.67 (USB_DP)
/rp-core/RST_BTN: D5.3, SW1.1
/rp-core/RUN: D5.1, R9.2, R13.2, TP7.1, U5.35 (RUN)
/rp-core/SWCLK: TP4.1, U5.33 (SWCLK)
/rp-core/SWDIO: TP5.1, U5.34 (SWDIO)
/rp-core/VREG_AVDD: C16.1, R12.2, U5.61 (VREG_AVDD)
/rp-core/XIN: C30.1, U5.30 (XIN), Y1.1
/rp-core/XOUT: R18.1, U5.31 (XOUT)
/rp-core/XOUT_Y: C31.1, R18.2, Y1.3
DVDD: C14.1, C15.1, C26.1, C27.1, L2.1, TP3.1, U5.10 (DVDD), U5.32 (DVDD), U5.51 (DVDD), U5.65 (VREG_FB)
GND: C14.2, C15.2, C16.2, C17.2, C18.2, C19.2, C20.2, C24.2, C25.2, C26.2, C27.2, C28.2, C29.2, C30.2, C31.2, C34.2, C36.2, C37.2, C38.2, C39.2, SW1.2, SW2.2, TP6.1, U5.62 (VREG_PGND), U5.81 (GND), Y1.2 (G), Y1.4 (G); also elsewhere on the board

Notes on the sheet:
Supplies (RP2350 datasheet 6.3.7): IOVDD, QSPI_IOVDD, USB_OTP_VDD, ADC_AVDD and VREG_VIN on +3V3_RP, the AP2112K LDO that rises with +5V; the core regulator switches VREG_LX through 3.3 uH onto DVDD (VREG_FB senses it), its analog supply VREG_AVDD through 33R / 4.7 uF. One 100 nF at every supply pi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

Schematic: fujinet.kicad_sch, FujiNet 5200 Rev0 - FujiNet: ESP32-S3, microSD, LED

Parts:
C3: 22uF; C_0805_2012Metric; MPN CL21A226MAQNNNE; LCSC C45783
C4, C32: 100nF; C_0603_1608Metric; MPN CC0603KRX7R9BB104; LCSC C14663
C5: 10uF; C_0603_1608Metric; MPN CL10A106KP8NNNC; LCSC C19702
C8: 1uF; C_0603_1608Metric; MPN CL10A105KB8NNNC; LCSC C15849
D6: WS2812B-2020-V6; LED_WS2812B-2020_PLCC4_2.0x2.0mm; MPN WS2812B-2020-V6; LCSC C52917434
J3: microSD; TF-SMD_TF-015; MPN TF-015; LCSC C113206
R4, R6: 10k; R_0603_1608Metric; MPN 0603WAF1002T5E; LCSC C25804
R19: 330R; R_0603_1608Metric; MPN 0603WAF3300T5E; LCSC C23138
RN1: 4x10k; R_Array_Convex_4x0603; MPN 4D03WGJ0103T5E; LCSC C29718
SW3: S3_RST; SW_SPST_TS-1187A; MPN TS-1187A-B-A-B; LCSC C318884
SW4: S3_BOOT; SW_SPST_TS-1187A; MPN TS-1187A-B-A-B; LCSC C318884
U1: ESP32-S3-WROOM-1-N16R8; ESP32-S3-WROOM-1; MPN ESP32-S3-WROOM-1-N16R8; LCSC C2913202

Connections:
+3V3: C3.1, C4.1, C5.1, J3.4 (VDD), R4.1, R6.1, RN1.5 (R4.2), RN1.6 (R3.2), RN1.7 (R2.2), RN1.8 (R1.2), U1.2 (3V3); also elsewhere on the board
+5V: C32.1, D6.4 (VDD); also elsewhere on the board
/BOOTSEL_CTL: U1.5 (IO5); also elsewhere on the board
/RUN_CTL: U1.4 (IO4); also elsewhere on the board
/S3_EN: C8.1, R6.2, SW3.1, U1.3 (EN); also elsewhere on the board
/S3_IO0: SW4.1, U1.27 (IO0); also elsewhere on the board
/S3_RXD: U1.36 (RXD0); also elsewhere on the board
/S3_TXD: U1.37 (TXD0); also elsewhere on the board
/USB_DM: U1.13 (USB_D-); also elsewhere on the board
/USB_DP: U1.14 (USB_D+); also elsewhere on the board
/fujinet/LED_STRIP: R19.1, U1.25 (IO48)
/fujinet/SD_CD: J3.9 (CD), R4.2, U1.35 (IO42)
/fujinet/SD_CS: J3.2 (DAT3/CS), RN1.1 (R1.1), U1.34 (IO41)
/fujinet/SD_DAT1: J3.8 (DAT1), RN1.3 (R3.1)
/fujinet/SD_DAT2: J3.1 (DAT2), RN1.4 (R4.1)
/fujinet/SD_MISO: J3.7 (DAT0/DO), RN1.2 (R2.1), U1.33 (IO40)
/fujinet/SD_MOSI: J3.3 (CMD/DI), U1.31 (IO38)
/fujinet/SD_SCK: J3.5 (CLK), U1.32 (IO39)
/fujinet/WS_DIN: D6.3 (DIN), R19.2
GND: C3.2, C4.2, C5.2, C8.2, C32.2, D6.2 (VSS), J3.6 (VSS), J3.10 (SH), J3.11 (SH), J3.12 (SH), J3.13 (SH), SW3.2, SW4.2, U1.1 (GND), U1.40 (GND), U1.41 (GND); also elsewhere on the board

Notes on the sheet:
ESP32-S3-WROOM-1-N16R8: the FujiNet (fujiversal-atari5200.h pin map). EN: 10k / 1 uF power-on delay. The S3_RST button, the cart RESET (rp-core, through the BAT54C) and the USB bridge's auto-program pair (usb sheet) all pull it low; S3_BOOT and the same pair pull IO0. IO4 / IO5 drive the RP2354B's 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

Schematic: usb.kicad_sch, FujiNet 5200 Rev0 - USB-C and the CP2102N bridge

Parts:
C1: 1uF; C_0603_1608Metric; MPN CL10A105KB8NNNC; LCSC C15849
C2, C6: 100nF; C_0603_1608Metric; MPN CC0603KRX7R9BB104; LCSC C14663
C7: 4.7uF; C_0603_1608Metric; MPN CL10A475KO8NNNC; LCSC C19666
D1, D2, D3: ESD5Z5.0T1G; D_SOD-523; MPN ESD5Z5.0T1G; LCSC C82044
J2: USB-C; USB_C_Receptacle_HRO_TYPE-C-31-M-12; MPN TYPE-C-31-M-12; LCSC C165948
R1, R2: 5.1k; R_0603_1608Metric; MPN 0603WAF5101T5E; LCSC C23186
R5: 10k; R_0603_1608Metric; MPN 0603WAF1002T5E; LCSC C25804
R10: 22k; R_0603_1608Metric; MPN 0603WAF2202T5E; LCSC C31850
R11: 47k; R_0603_1608Metric; MPN 0603WAF4702T5E; LCSC C25819
U2: CP2102N-A02-GQFN28; QFN-28-1EP_5x5mm_P0.5mm_EP3.35x3.35mm; MPN CP2102N-A02-GQFN28R; LCSC C964632
U3: UMH3N; SOT-363_SC-70-6; MPN UMH3N; LCSC C62892

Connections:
+3V3: C6.1, C7.1, R5.1, U2.6 (VDD), U2.7 (VREGIN); also elsewhere on the board
/S3_EN: U3.6 (C1); also elsewhere on the board
/S3_IO0: U3.3 (C2); also elsewhere on the board
/S3_RXD: U2.26 (TXD); also elsewhere on the board
/S3_TXD: U2.25 (RXD); also elsewhere on the board
/usb/CC1: J2.A5 (CC1), R1.1
/usb/CC2: J2.B5 (CC2), R2.1
/usb/CP_RST: R5.2, U2.9 (~RST)
/usb/UART_DTR: U2.28 (~DTR), U3.2 (B1), U3.4 (E2)
/usb/UART_RTS: U2.24 (~RTS), U3.1 (E1), U3.5 (B2)
/usb/UBRG_DM: D3.1 (K), J2.A7 (D-), J2.B7 (D-), U2.5 (D-)
/usb/UBRG_DP: D2.1 (K), J2.A6 (D+), J2.B6 (D+), U2.4 (D+)
/usb/VBUS_SNS: R10.2, R11.1, U2.8 (VBUS)
GND: C1.2, C2.2, C6.2, C7.2, D1.2 (A), D2.2 (A), D3.2 (A), J2.A1 (GND), J2.A12 (GND), J2.B1 (GND), J2.B12 (GND), J2.SH (SHIELD), R1.2, R2.2, R11.2, U2.3 (GND), U2.23 (~CTS), U2.29 (GND); also elsewhere on the board
VBUS: C1.1, C2.1, D1.1 (K), J2.A4 (VBUS), J2.A9 (VBUS), J2.B4 (VBUS), J2.B9 (VBUS), R10.1; also elsewhere on the board

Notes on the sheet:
esptool's auto-program pair, as on the ESP32-S3-DevKitC-1: DTR low with RTS high pulls EN low; RTS low with DTR high pulls IO0 low; both high or both low leave the S3 alone.

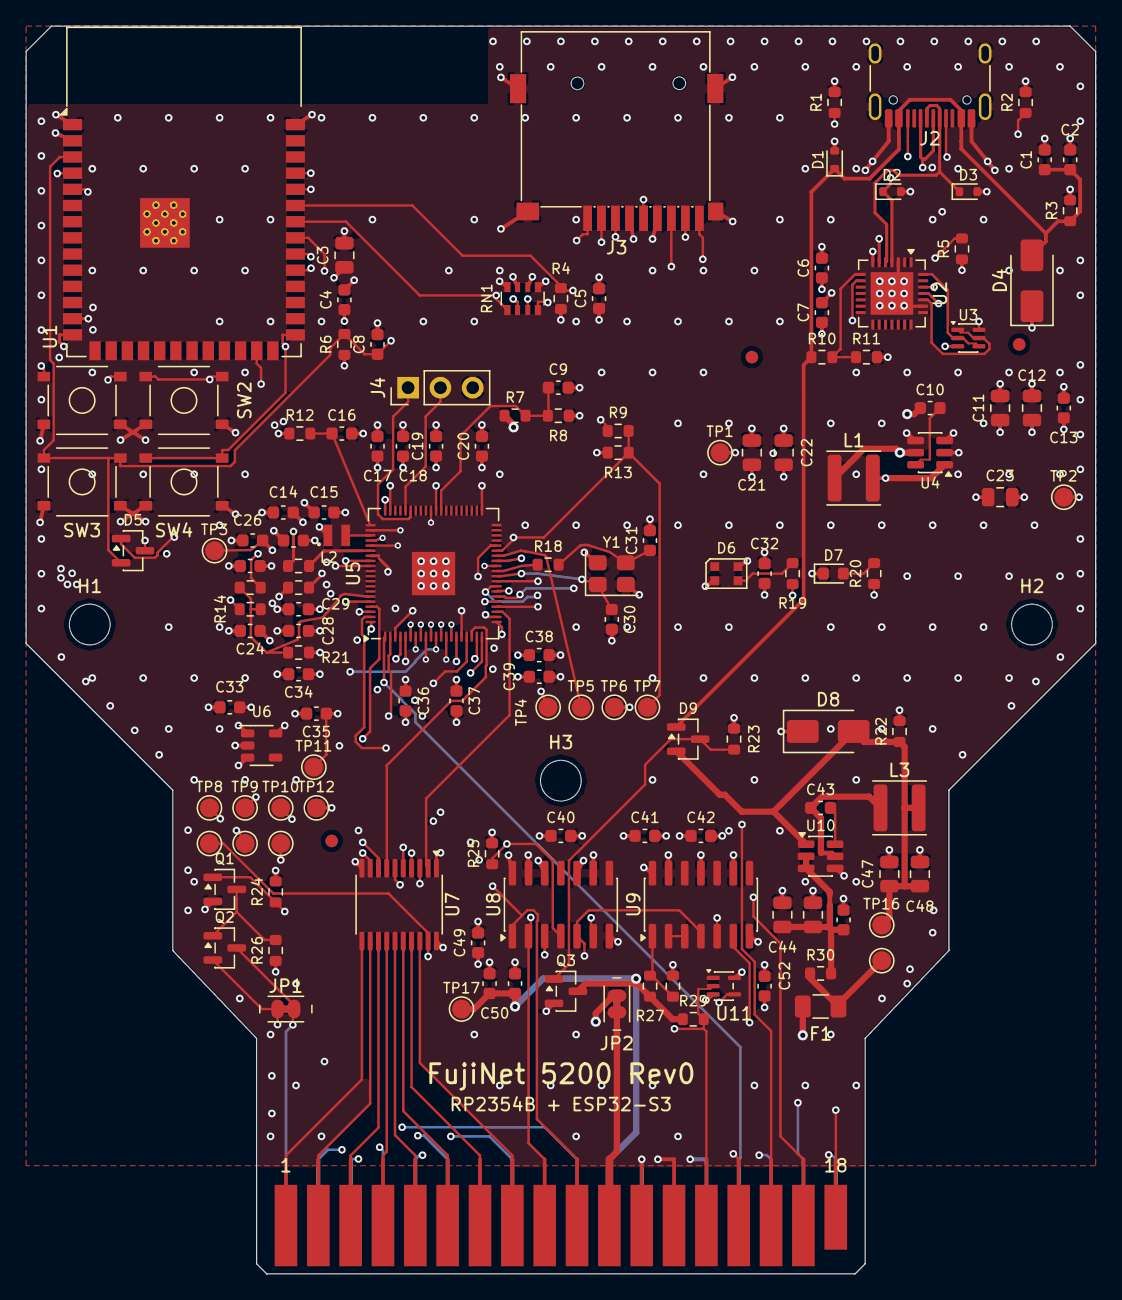
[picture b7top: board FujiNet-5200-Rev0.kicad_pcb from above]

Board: 6 copper layers, 84.0 x 98.0 mm, 145 parts (0 on the bottom side), 105 nets.

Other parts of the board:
FID1, FID2, FID3: Fiducial_1mm_Mask2mm
H1, H2, H3: MountingHole_3.2mm_NPTH

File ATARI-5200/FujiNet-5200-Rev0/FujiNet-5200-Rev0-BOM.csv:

"Refs","Value","Footprint","MPN","Manufacturer","LCSC","Description","DNP"
"C3,C11,C12,C21,C22,C23,C44,C45,C47,C48","22uF","C_0805_2012Metric","CL21A226MAQNNNE","Samsung Electro-Mechanics","C45783","S3 bulk (WiFi TX bursts)",""
"C1,C8,C33,C35","1uF","C_0603_1608Metric","CL10A105KB8NNNC","Samsung Electro-Mechanics","C15849","EN power-on delay",""
"C7,C16,C25,C27","4.7uF","C_0603_1608Metric","CL10A475KO8NNNC","Samsung Electro-Mechanics","C19666","VREG_VIN bulk (LDO rail)",""
"C30,C31","15pF","C_0603_1608Metric","CL10C150JB8NNNC","Samsung Electro-Mechanics","C1644","crystal load",""
"C5,C24,C42,C51","10uF","C_0603_1608Metric","CL10A106KP8NNNC","Samsung Electro-Mechanics","C19702","5V logic domain bulk",""
"C2,C4,C6,C9,C10,C13,C14,C15,C17,C18,C19,C20,C26,C28,C29,C32,C34,C36,C37,C38,C39,C40,C41,C43,C46,C49,C50,C52","100nF","C_0603_1608Metric","CC0603KRX7R9BB104","YAGEO","C14663","74HCT541 VCC decoupling",""
"D1,D2,D3","ESD5Z5.0T1G","D_SOD-523","ESD5Z5.0T1G","onsemi","C82044","ESD",""
"D4,D8","SS34","D_SMA","SS34","MDD (Microdiode Semiconductor)","C8678","USB VBUS OR-ing (no back-feed into the console or the host)",""
"D5,D9","BAT54C","SOT-23","BAT54C,215","Nexperia","C37704","RESET steering, common cathode",""
"D6","WS2812B-2020-V6","LED_WS2812B-2020_PLCC4_2.0x2.0mm","WS2812B-2020-V6","Worldsemi","C52917434","status LED on +5V (datasheet VDD 3.7-5.3 V; VIH 2.7 V takes the S3 3.3 V data directly)",""
"D7","red","LED_0603_1608Metric","KT-0603R","Hubei KENTO Elec","C2286","activity LED (GPIO27)",""
"F1","0.35A","Fuse_1206_3216Metric","1206L035/30WR","Littelfuse","C2153989","PTC 0.35 A hold, 30 V: the adapter is never loaded by a cart fault",""
"J2","USB-C","USB_C_Receptacle_HRO_TYPE-C-31-M-12","TYPE-C-31-M-12","Korean Hroparts Elec","C165948","power + S3 programming",""
"J3","microSD","TF-SMD_TF-015","TF-015","SOFNG","C113206","microSD push-push, SPI mode",""
"J4","DBG UART","PinHeader_1x03_P2.54mm_Vertical","PZ254V-11-03P","XFCN","C2937625","RP debug UART, 3.3 V: 1 TX (GPIO44), 2 RX (GPIO45), 3 GND; fit for bring-up","DNP"
"L1","6.8uH","L_Sunlord_SWPA4030S","SWPA4030S6R8MT","Sunlord","C62684","buck inductor",""
"L2","3.3uH","RPI_L_AOTA-B201610S3R3","AOTA-B201610S3R3-101-T","Abracon","C42411119","RP2350 core SMPS inductor",""
"L3","4.7uH","L_Sunlord_SWPA4030S","SWPA4030S4R7MT","Sunlord","C57269","raw DC buck inductor (datasheet Table 3: 4.7 uH at 5 V)",""
"Q1,Q2","2N7002","SOT-23","2N7002","Jiangsu Changjing (JSCJ)","C8545","interlock switch (DNP): D = CI2 (pin 36), S = CI1 (pin 18)","DNP"
"Q3","AO3401A","SOT-23","AO3401A","Alpha & Omega Semiconductor","C15127","console 5V switch: G = CONS_OFF, S = +5V, D = CONS_5V; body diode CONS_5V -> +5V",""
"R1,R2","5.1k","R_0603_1608Metric","0603WAF5101T5E","UNI-ROYAL","C23186","UFP Rd",""
"R11","47k","R_0603_1608Metric","0603WAF4702T5E","UNI-ROYAL","C25819","VBUS sense divider",""
"R12","33R","R_0603_1608Metric","0603WAF330JT5E","UNI-ROYAL","C23140","VREG_AVDD filter",""
"R4,R5,R6,R13,R21","10k","R_0603_1608Metric","0603WAF1002T5E","UNI-ROYAL","C25804","RUN pull-up",""
"R16,R17","27R","R_0603_1608Metric","0603WAF270JT5E","UNI-ROYAL","C25190","USB series",""
"R19","330R","R_0603_1608Metric","0603WAF3300T5E","UNI-ROYAL","C23138","WS2812 data series",""
"R9,R14,R15,R18,R20","1k","R_0603_1608Metric","0603WAF1001T5E","UNI-ROYAL","C21190","activity LED series",""
"R24","4.7k","R_0603_1608Metric","0603WAF4701T5E","UNI-ROYAL","C23162","GPIO28 low until the firmware drives it (RP2350-E9: <= 8.2k; DNP)","DNP"
"R3,R22,R25,R29","4.7k","R_0603_1608Metric","0603WAF4701T5E","UNI-ROYAL","C23162","BUF_EN low until the firmware drives it (RP2350-E9: <= 8.2k)",""
"R26","10k","R_0603_1608Metric","0603WAF1002T5E","UNI-ROYAL","C25804","interlock switch closed by default (DNP)","DNP"
"R10,R27","22k","R_0603_1608Metric","0603WAF2202T5E","UNI-ROYAL","C31850","console 5V sense divider",""
"R7,R8,R23,R28","100k","R_0603_1608Metric","0603WAF1003T5E","UNI-ROYAL","C25803","console 5V sense -> 0.82 x CONS_5V",""
"R30","2.2R","R_0603_1608Metric","RC0603FR-072R2L","YAGEO","C112307","inrush limit into the buck input",""
"RN1","4x10k","R_Array_Convex_4x0603","4D03WGJ0103T5E","UNI-ROYAL","C29718","SD pull-ups",""
"SW1","RESET","SW_SPST_TS-1187A","TS-1187A-B-A-B","XKB Connection","C318884","cart RESET: RP RUN + S3 EN via BAT54C",""
"SW2","BOOTSEL","SW_SPST_TS-1187A","TS-1187A-B-A-B","XKB Connection","C318884","RP2354 BOOTSEL (hold while pressing RESET)",""
"SW3","S3_RST","SW_SPST_TS-1187A","TS-1187A-B-A-B","XKB Connection","C318884","ESP32-S3 EN",""
"SW4","S3_BOOT","SW_SPST_TS-1187A","TS-1187A-B-A-B","XKB Connection","C318884","ESP32-S3 BOOT (IO0)",""
"U1","ESP32-S3-WROOM-1-N16R8","ESP32-S3-WROOM-1","ESP32-S3-WROOM-1-N16R8","Espressif","C2913202","FujiNet core (fujiversal-atari5200)",""
"U2","CP2102N-A02-GQFN28","QFN-28-1EP_5x5mm_P0.5mm_EP3.35x3.35mm","CP2102N-A02-GQFN28R","Silicon Labs","C964632","USB-UART for S3 flashing/console (self-powered)",""
"U3","UMH3N","SOT-363_SC-70-6","UMH3N","Jiangsu Changjing (JSCJ)","C62892","esptool auto-program (DevKitC-1 style)",""
"U4","AP63203WU","TSOT-23-6","AP63203WU-7","Diodes Incorporated","C780769","3.3V 2A buck",""
"U5","RP2354B","QFN-80-1EP_10x10mm_P0.4mm_EP3.4x3.4mm","RP2354B","Raspberry Pi","C39843328","RP2350B + 2MB flash in package; cart bus server",""
"U6","AP2112K-3.3","SOT-23-5","AP2112K-3.3TRG1","Diodes Incorporated","C51118","RP2354B 3.3V LDO (IOVDD, VREG_VIN, VREG_AVDD), 600mA, fast start",""
"U7","74HCT541","TSSOP-20_4.4x6.5mm_P0.65mm","SN74HCT541PWR","Texas Instruments","C436096","D0-D7 driver: drives only while /OE1 (served) and /OE2 (either enable) are low",""
"U8","74HCT08","SOIC-14_3.9x8.7mm_P1.27mm","SN74HCT08DR","Texas Instruments","C6767","EN_ANY_N = /EN40 & /EN80; SERVE = PWR_OK & BUF_EN",""
"U9","74HCT14","SOIC-14_3.9x8.7mm_P1.27mm","SN74HCT14DR","Texas Instruments","C6769","PWR_OK from the console 5V sense; SERVE inversion",""
"U10","AP63205WU","TSOT-23-6","AP63205WU-7","Diodes Incorporated","C2071056","edge raw DC (9-13 V) -> 5 V, 2 A buck",""
"U11","74LVC1G17","SOT-353_SC-70-5","74LVC1G17GW,125","Nexperia","C426705","PHI2 Schmitt buffer: CMOS thresholds for the diode-isolated clock",""
"Y1","12MHz","Crystal_SMD_3225-4Pin_3.2x2.5mm","ABM8-272-T3","Abracon","C20625731","RP2350 12 MHz crystal",""
